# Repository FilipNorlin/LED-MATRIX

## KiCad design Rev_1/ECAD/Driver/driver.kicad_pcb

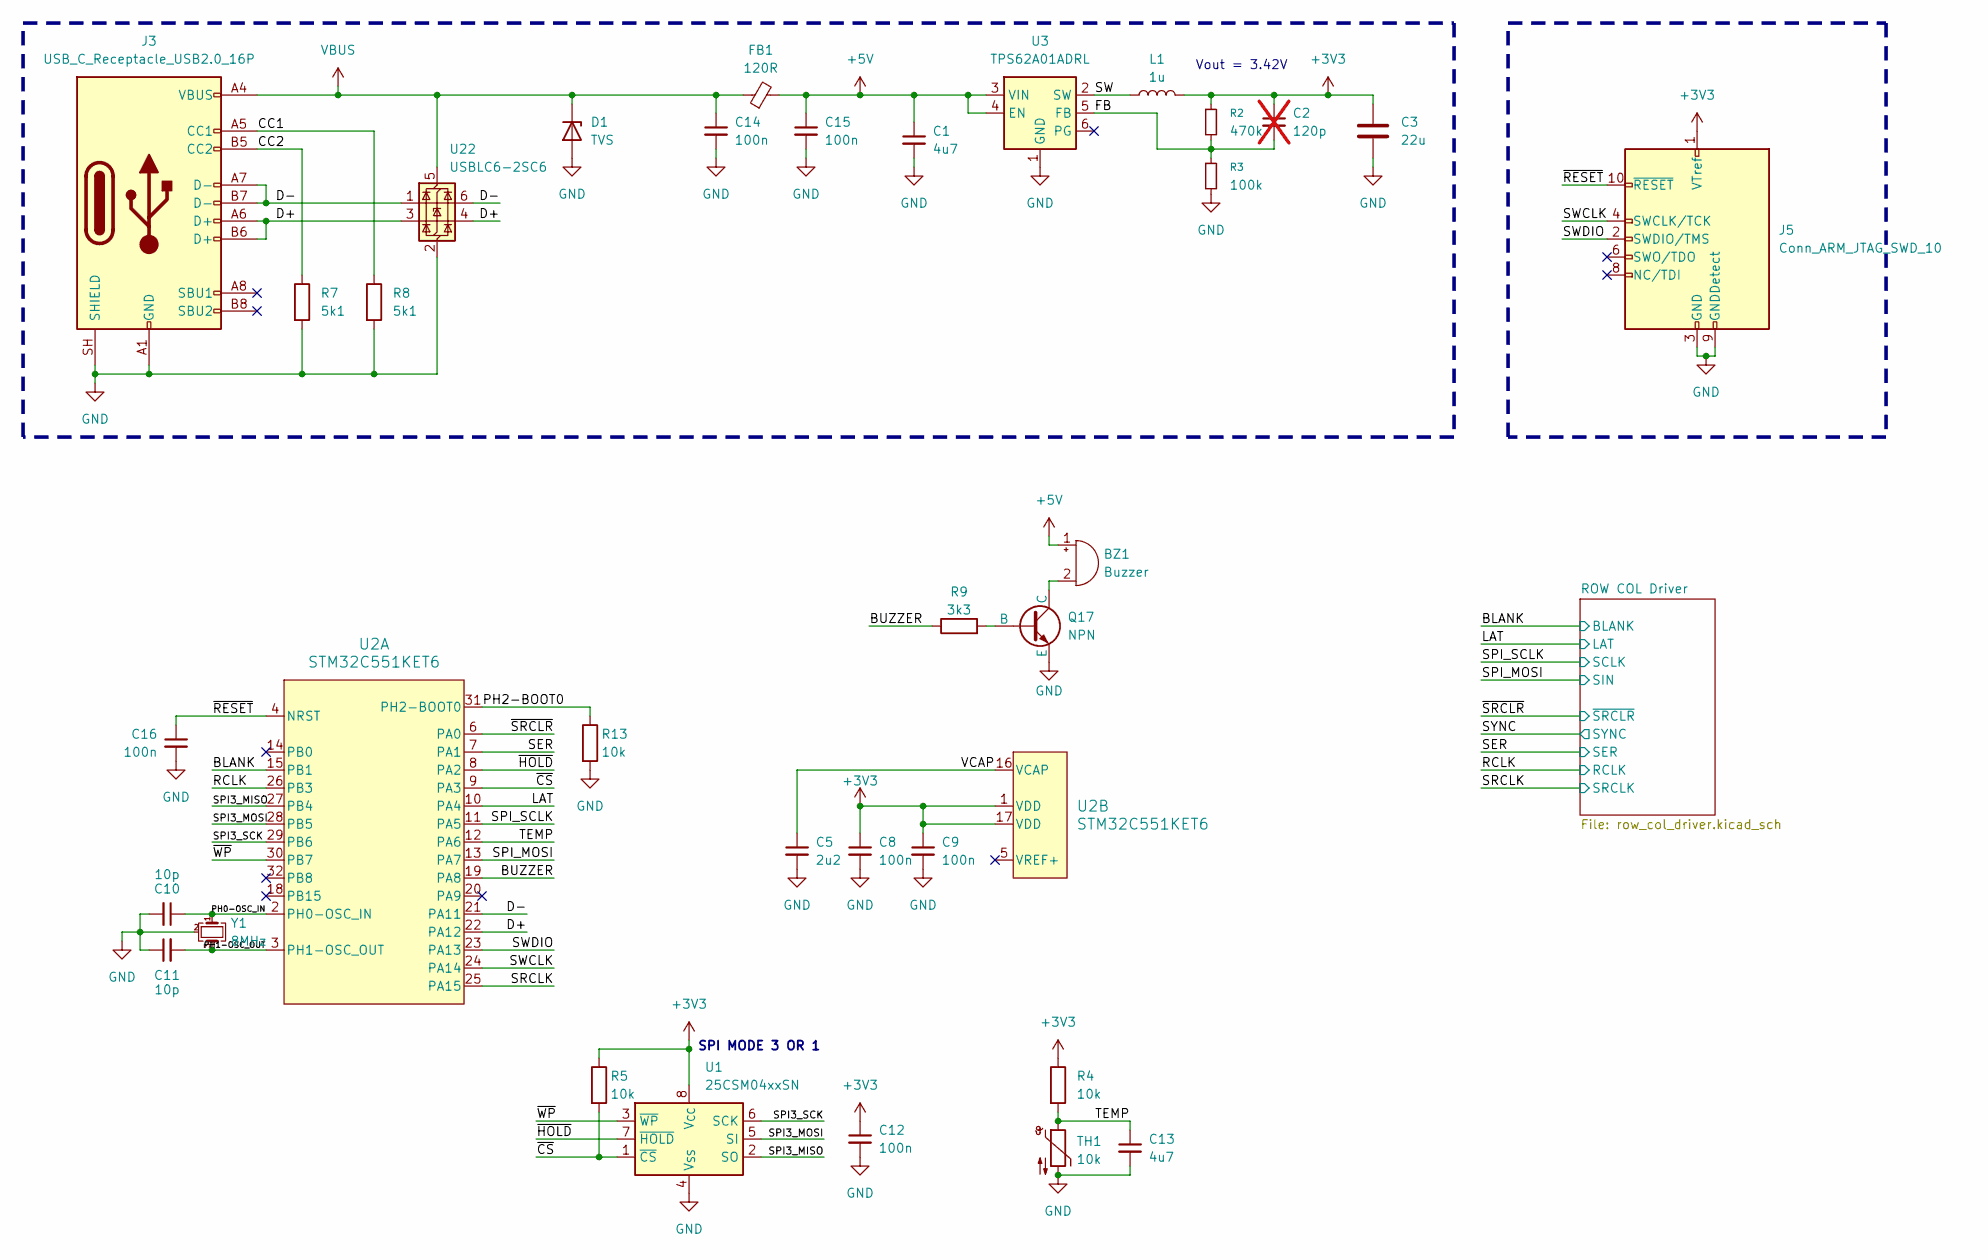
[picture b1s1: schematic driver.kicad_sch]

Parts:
BZ1: Buzzer; CPT120378SMTTR
C1, C13: 4u7; C_0805_2012Metric
C2: 120p; C_0603_1608Metric; not fitted
C3: 22u; C_0805_2012Metric
C5: 2u2; C_0603_1608Metric
C8, C9, C12, C14, C15: 100n; C_0805_2012Metric
C10, C11: 10p; C_0603_1608Metric
C16: 100n; C_0603_1608Metric
D1: TVS; D_SOD-123F
FB1: 120R; L_0805_2012Metric
J3: USB_C_Receptacle_USB2.0_16P; USB_C_Receptacle_GCT_USB4105-xx-A_16P_TopMnt_Horizontal
J5: Conn_ARM_JTAG_SWD_10; PinHeader_2x05_P1.27mm_Vertical_SMD
L1: 1u; L_0805_2012Metric; Mouser No: 187-CB201210AG1R0MPE
Q17: NPN; SOT-23
R2: 470k; R_0603_1608Metric_Pad0.98x0.95mm_HandSolder
R3: 100k; R_0805_2012Metric
R4, R5, R13: 10k; R_0805_2012Metric
R7, R8: 5k1; R_0805_2012Metric
R9: 3k3; R_0603_1608Metric
TH1: 10k; R_0603_1608Metric
U1: 25CSM04xxSN; SOIC-8_3.9x4.9mm_P1.27mm
U2: STM32C551KET6; LQFP-32_7x7mm_P0.8mm
U3: TPS62A01ADRL; SOT-563
U22: USBLC6-2SC6; SOT-23-6
Y1: 8MHz; Crystal_SMD_3225-4Pin_3.2x2.5mm

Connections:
+3V3: C2.1, C3.1, C8.1, C9.1, C12.1, J5.1 (VTref), L1.2, R2.1, R4.1, R5.1, U1.8 (V_{CC}), U2.1 (VDD), U2.17 (VDD); also elsewhere on the board
+5V: BZ1.1 (+), C1.1, C15.1, FB1.2, U3.3 (VIN), U3.4 (EN)
/BLANK: U2.15 (PB1); also elsewhere on the board
/BUZZER: R9.1, U2.19 (PA8)
/CC1: J3.A5 (CC1), R8.1
/CC2: J3.B5 (CC2), R7.1
/D+: J3.A6 (D+), J3.B6 (D+), U2.22 (PA12), U22.3 (I/O2), U22.4 (I/O2)
/D-: J3.A7 (D-), J3.B7 (D-), U2.21 (PA11), U22.1 (I/O1), U22.6 (I/O1)
/FB: C2.2, R2.2, R3.1, U3.5 (FB)
/LAT: U2.10 (PA4); also elsewhere on the board
/PH0-OSC_IN: C10.1, U2.2 (PH0-OSC_IN), Y1.1
/PH1-OSC_OUT: C11.2, U2.3 (PH1-OSC_OUT), Y1.3
/PH2-BOOT0: R13.1, U2.31 (PH2-BOOT0)
/RCLK: U2.26 (PB3); also elsewhere on the board
/SER: U2.7 (PA1); also elsewhere on the board
/SPI3_MISO: U1.2 (SO), U2.27 (PB4)
/SPI3_MOSI: U1.5 (SI), U2.28 (PB5)
/SPI3_SCK: U1.6 (SCK), U2.29 (PB6)
/SPI_MOSI: U2.13 (PA7); also elsewhere on the board
/SPI_SCLK: U2.11 (PA5); also elsewhere on the board
/SRCLK: U2.25 (PA15); also elsewhere on the board
/SW: L1.1, U3.2 (SW)
/SWCLK: J5.4 (SWCLK/TCK), U2.24 (PA14)
/SWDIO: J5.2 (SWDIO/TMS), U2.23 (PA13)
/TEMP: C13.1, R4.2, TH1.1, U2.12 (PA6)
/VCAP: C5.1, U2.16 (VCAP)
/~CS: R5.2, U1.1 (~CS), U2.9 (PA3)
/~HOLD: U1.7 (~HOLD), U2.8 (PA2)
/~RESET: C16.1, J5.10 (~RESET), U2.4 (NRST)
/~SRCLR: U2.6 (PA0); also elsewhere on the board
/~WP: U1.3 (~WP), U2.30 (PB7)
GND: C1.2, C3.2, C5.2, C8.2, C9.2, C10.2, C11.1, C12.2, C13.2, C14.2, C15.2, C16.2, D1.2 (A), J3.A1 (GND), J3.A12 (GND), J3.B1 (GND), J3.B12 (GND), J3.SH (SHIELD), J5.3 (GND), J5.5 (GND), J5.9 (GNDDetect), Q17.3 (E), R3.2, R7.2, R8.2, R13.2, TH1.2, U1.4 (V_{SS}), U3.1 (GND), U22.2 (GND), Y1.2 (G), Y1.4 (G); also elsewhere on the board
unnamed: BZ1.2 (-), Q17.1 (C)
unnamed: Q17.2 (B), R9.2
VBUS: C14.1, D1.1 (K), FB1.1, J3.A4 (VBUS), J3.A9 (VBUS), J3.B4 (VBUS), J3.B9 (VBUS), U22.5 (VBUS)

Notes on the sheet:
Vout = 3.42V
SPI MODE 3 OR 1

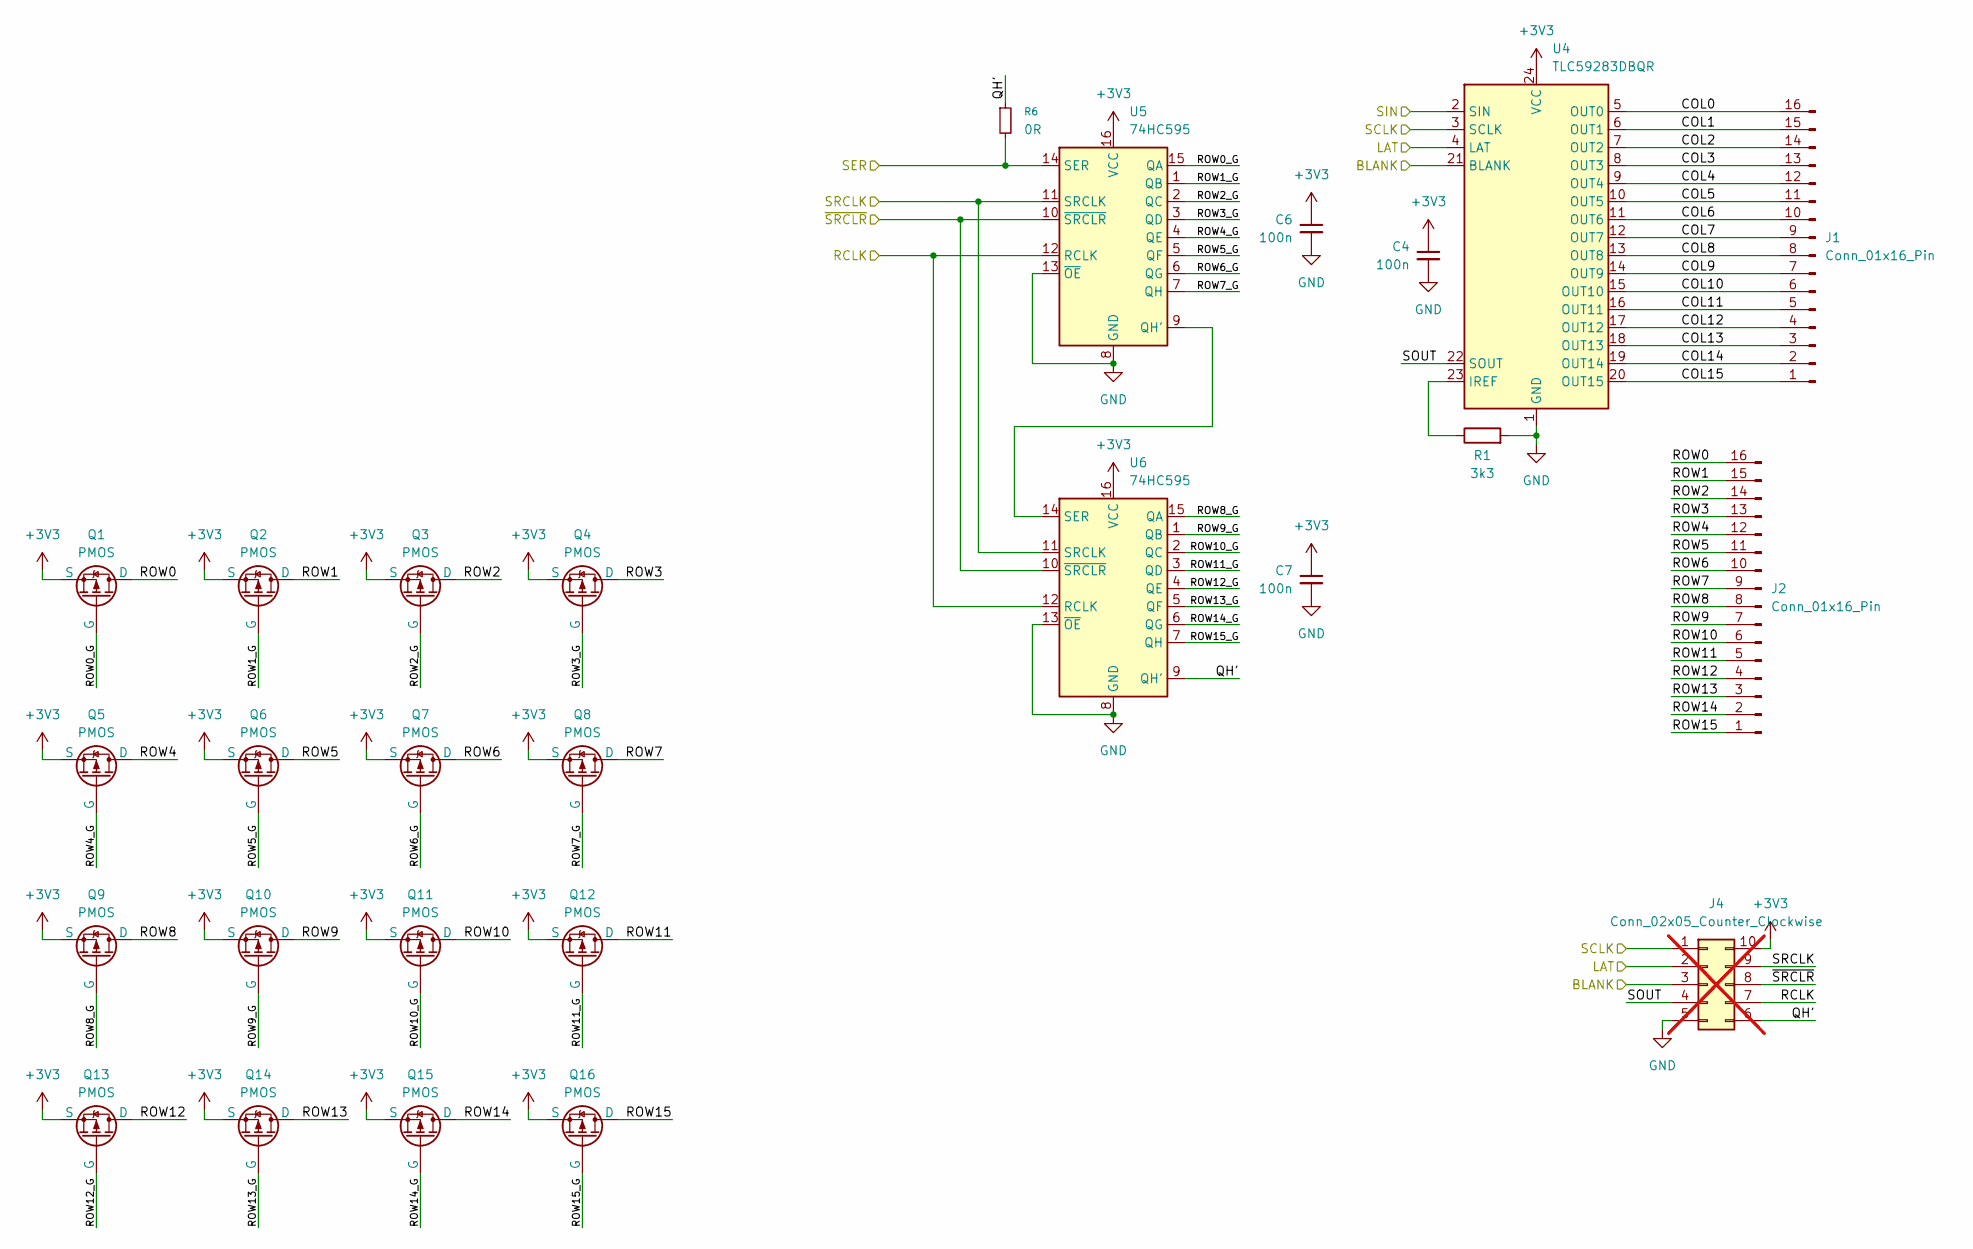
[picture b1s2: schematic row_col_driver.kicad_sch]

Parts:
C4, C6, C7: 100n; C_0805_2012Metric
J1, J2: Conn_01x16_Pin; PinSocket_1x16_P2.54mm_Vertical
J4: Conn_02x05_Counter_Clockwise; not fitted
Q1, Q2, Q3, Q4, Q5, Q6, Q7, Q8, Q9, Q10, Q11, Q12, Q13, Q14, Q15, Q16: PMOS; SOT-23
R1: 3k3; R_0603_1608Metric
R6: 0R; R_0603_1608Metric
U4: TLC59283DBQR; QSOP-24_3.9x8.7mm_P0.635mm; Mouser Part Number 595-TLC59283DBQR
U5, U6: 74HC595; SOIC-16_3.9x9.9mm_P1.27mm

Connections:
+3V3: C4.1, C6.1, C7.1, J4.10, Q1.3 (S), Q2.3 (S), Q3.3 (S), Q4.3 (S), Q5.3 (S), Q6.3 (S), Q7.3 (S), Q8.3 (S), Q9.3 (S), Q10.3 (S), Q11.3 (S), Q12.3 (S), Q13.3 (S), Q14.3 (S), Q15.3 (S), Q16.3 (S), U4.24 (VCC), U5.16 (VCC), U6.16 (VCC); also elsewhere on the board
/BLANK: J4.3, U4.21 (BLANK); also elsewhere on the board
/LAT: J4.2, U4.4 (LAT); also elsewhere on the board
/RCLK: U5.12 (RCLK), U6.12 (RCLK); also elsewhere on the board
/ROW COL Driver/COL0: J1.16, U4.5 (OUT0)
/ROW COL Driver/COL1: J1.15, U4.6 (OUT1)
/ROW COL Driver/COL2: J1.14, U4.7 (OUT2)
/ROW COL Driver/COL3: J1.13, U4.8 (OUT3)
/ROW COL Driver/COL4: J1.12, U4.9 (OUT4)
/ROW COL Driver/COL5: J1.11, U4.10 (OUT5)
/ROW COL Driver/COL6: J1.10, U4.11 (OUT6)
/ROW COL Driver/COL7: J1.9, U4.12 (OUT7)
/ROW COL Driver/COL8: J1.8, U4.13 (OUT8)
/ROW COL Driver/COL9: J1.7, U4.14 (OUT9)
/ROW COL Driver/COL10: J1.6, U4.15 (OUT10)
/ROW COL Driver/COL11: J1.5, U4.16 (OUT11)
/ROW COL Driver/COL12: J1.4, U4.17 (OUT12)
/ROW COL Driver/COL13: J1.3, U4.18 (OUT13)
/ROW COL Driver/COL14: J1.2, U4.19 (OUT14)
/ROW COL Driver/COL15: J1.1, U4.20 (OUT15)
/ROW COL Driver/QH': J4.6, R6.1, U6.9 (QH')
/ROW COL Driver/ROW0: J2.16, Q1.1 (D)
/ROW COL Driver/ROW0_G: Q1.2 (G), U5.15 (QA)
/ROW COL Driver/ROW1: J2.15, Q2.1 (D)
/ROW COL Driver/ROW1_G: Q2.2 (G), U5.1 (QB)
/ROW COL Driver/ROW2: J2.14, Q3.1 (D)
/ROW COL Driver/ROW2_G: Q3.2 (G), U5.2 (QC)
/ROW COL Driver/ROW3: J2.13, Q4.1 (D)
/ROW COL Driver/ROW3_G: Q4.2 (G), U5.3 (QD)
/ROW COL Driver/ROW4: J2.12, Q5.1 (D)
/ROW COL Driver/ROW4_G: Q5.2 (G), U5.4 (QE)
/ROW COL Driver/ROW5: J2.11, Q6.1 (D)
/ROW COL Driver/ROW5_G: Q6.2 (G), U5.5 (QF)
/ROW COL Driver/ROW6: J2.10, Q7.1 (D)
/ROW COL Driver/ROW6_G: Q7.2 (G), U5.6 (QG)
/ROW COL Driver/ROW7: J2.9, Q8.1 (D)
/ROW COL Driver/ROW7_G: Q8.2 (G), U5.7 (QH)
/ROW COL Driver/ROW8: J2.8, Q9.1 (D)
/ROW COL Driver/ROW8_G: Q9.2 (G), U6.15 (QA)
/ROW COL Driver/ROW9: J2.7, Q10.1 (D)
/ROW COL Driver/ROW9_G: Q10.2 (G), U6.1 (QB)
/ROW COL Driver/ROW10: J2.6, Q11.1 (D)
/ROW COL Driver/ROW10_G: Q11.2 (G), U6.2 (QC)
/ROW COL Driver/ROW11: J2.5, Q12.1 (D)
/ROW COL Driver/ROW11_G: Q12.2 (G), U6.3 (QD)
/ROW COL Driver/ROW12: J2.4, Q13.1 (D)
/ROW COL Driver/ROW12_G: Q13.2 (G), U6.4 (QE)
/ROW COL Driver/ROW13: J2.3, Q14.1 (D)
/ROW COL Driver/ROW13_G: Q14.2 (G), U6.5 (QF)
/ROW COL Driver/ROW14: J2.2, Q15.1 (D)
/ROW COL Driver/ROW14_G: Q15.2 (G), U6.6 (QG)
/ROW COL Driver/ROW15: J2.1, Q16.1 (D)
/ROW COL Driver/ROW15_G: Q16.2 (G), U6.7 (QH)
/ROW COL Driver/SOUT: J4.4, U4.22 (SOUT)
/SER: R6.2, U5.14 (SER); also elsewhere on the board
/SPI_MOSI: U4.2 (SIN); also elsewhere on the board
/SPI_SCLK: J4.1, U4.3 (SCLK); also elsewhere on the board
/SRCLK: U5.11 (SRCLK), U6.11 (SRCLK); also elsewhere on the board
/~SRCLR: U5.10 (~SRCLR), U6.10 (~SRCLR); also elsewhere on the board
GND: C4.2, C6.2, C7.2, J4.5, R1.2, U4.1 (GND), U5.8 (GND), U5.13 (~OE), U6.8 (GND), U6.13 (~OE); also elsewhere on the board
unnamed: R1.1, U4.23 (IREF)
unnamed: U5.9 (QH'), U6.14 (SER)

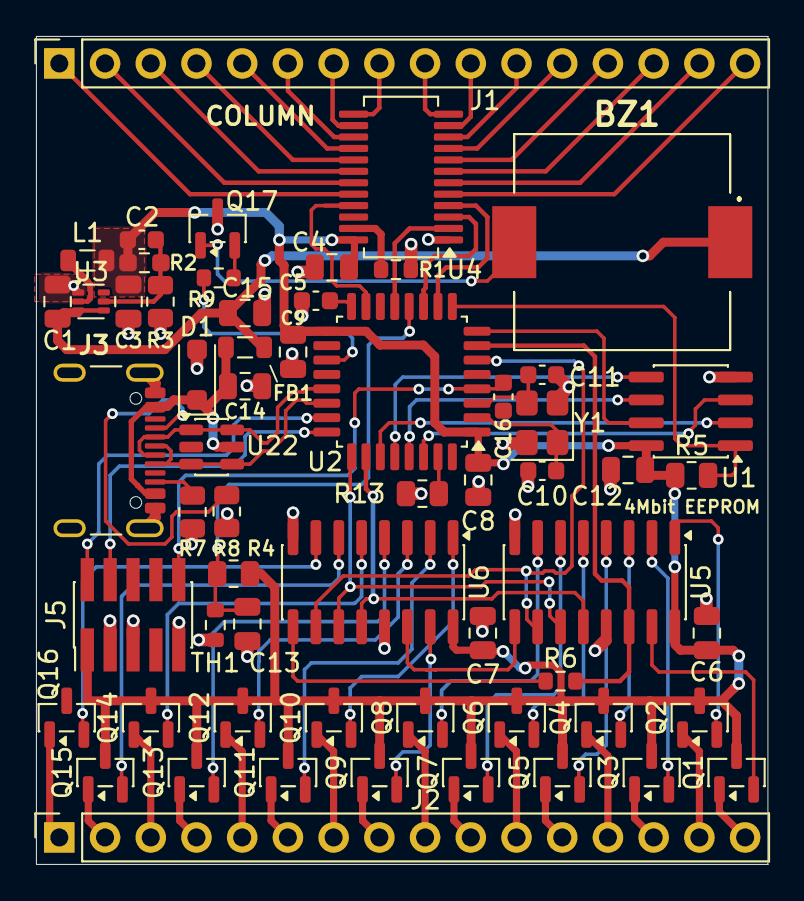
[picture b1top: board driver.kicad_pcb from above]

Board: 4 copper layers, 40.6 x 46.0 mm, 60 parts (0 on the bottom side), 86 nets.

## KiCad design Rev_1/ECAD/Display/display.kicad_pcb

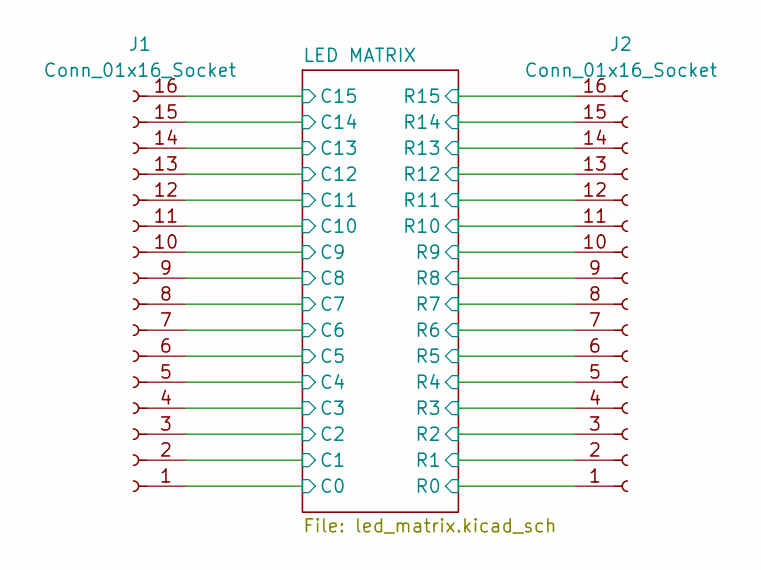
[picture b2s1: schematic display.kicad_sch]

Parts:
J1: Conn_01x16_Socket; PinHeader_1x16_P2.54mm_Vertical
J2: Conn_01x16_Socket; PinHeader_1x16_P2.54mm_Vertical_SMD_Pin1Left

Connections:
/LED MATRIX/C0: J1.1; also elsewhere on the board
/LED MATRIX/C1: J1.2; also elsewhere on the board
/LED MATRIX/C2: J1.3; also elsewhere on the board
/LED MATRIX/C3: J1.4; also elsewhere on the board
/LED MATRIX/C4: J1.5; also elsewhere on the board
/LED MATRIX/C5: J1.6; also elsewhere on the board
/LED MATRIX/C6: J1.7; also elsewhere on the board
/LED MATRIX/C7: J1.8; also elsewhere on the board
/LED MATRIX/C8: J1.9; also elsewhere on the board
/LED MATRIX/C9: J1.10; also elsewhere on the board
/LED MATRIX/C10: J1.11; also elsewhere on the board
/LED MATRIX/C11: J1.12; also elsewhere on the board
/LED MATRIX/C12: J1.13; also elsewhere on the board
/LED MATRIX/C13: J1.14; also elsewhere on the board
/LED MATRIX/C14: J1.15; also elsewhere on the board
/LED MATRIX/C15: J1.16; also elsewhere on the board
/LED MATRIX/R0: J2.1; also elsewhere on the board
/LED MATRIX/R1: J2.2; also elsewhere on the board
/LED MATRIX/R2: J2.3; also elsewhere on the board
/LED MATRIX/R3: J2.4; also elsewhere on the board
/LED MATRIX/R4: J2.5; also elsewhere on the board
/LED MATRIX/R5: J2.6; also elsewhere on the board
/LED MATRIX/R6: J2.7; also elsewhere on the board
/LED MATRIX/R7: J2.8; also elsewhere on the board
/LED MATRIX/R8: J2.9; also elsewhere on the board
/LED MATRIX/R9: J2.10; also elsewhere on the board
/LED MATRIX/R10: J2.11; also elsewhere on the board
/LED MATRIX/R11: J2.12; also elsewhere on the board
/LED MATRIX/R12: J2.13; also elsewhere on the board
/LED MATRIX/R13: J2.14; also elsewhere on the board
/LED MATRIX/R14: J2.15; also elsewhere on the board
/LED MATRIX/R15: J2.16; also elsewhere on the board

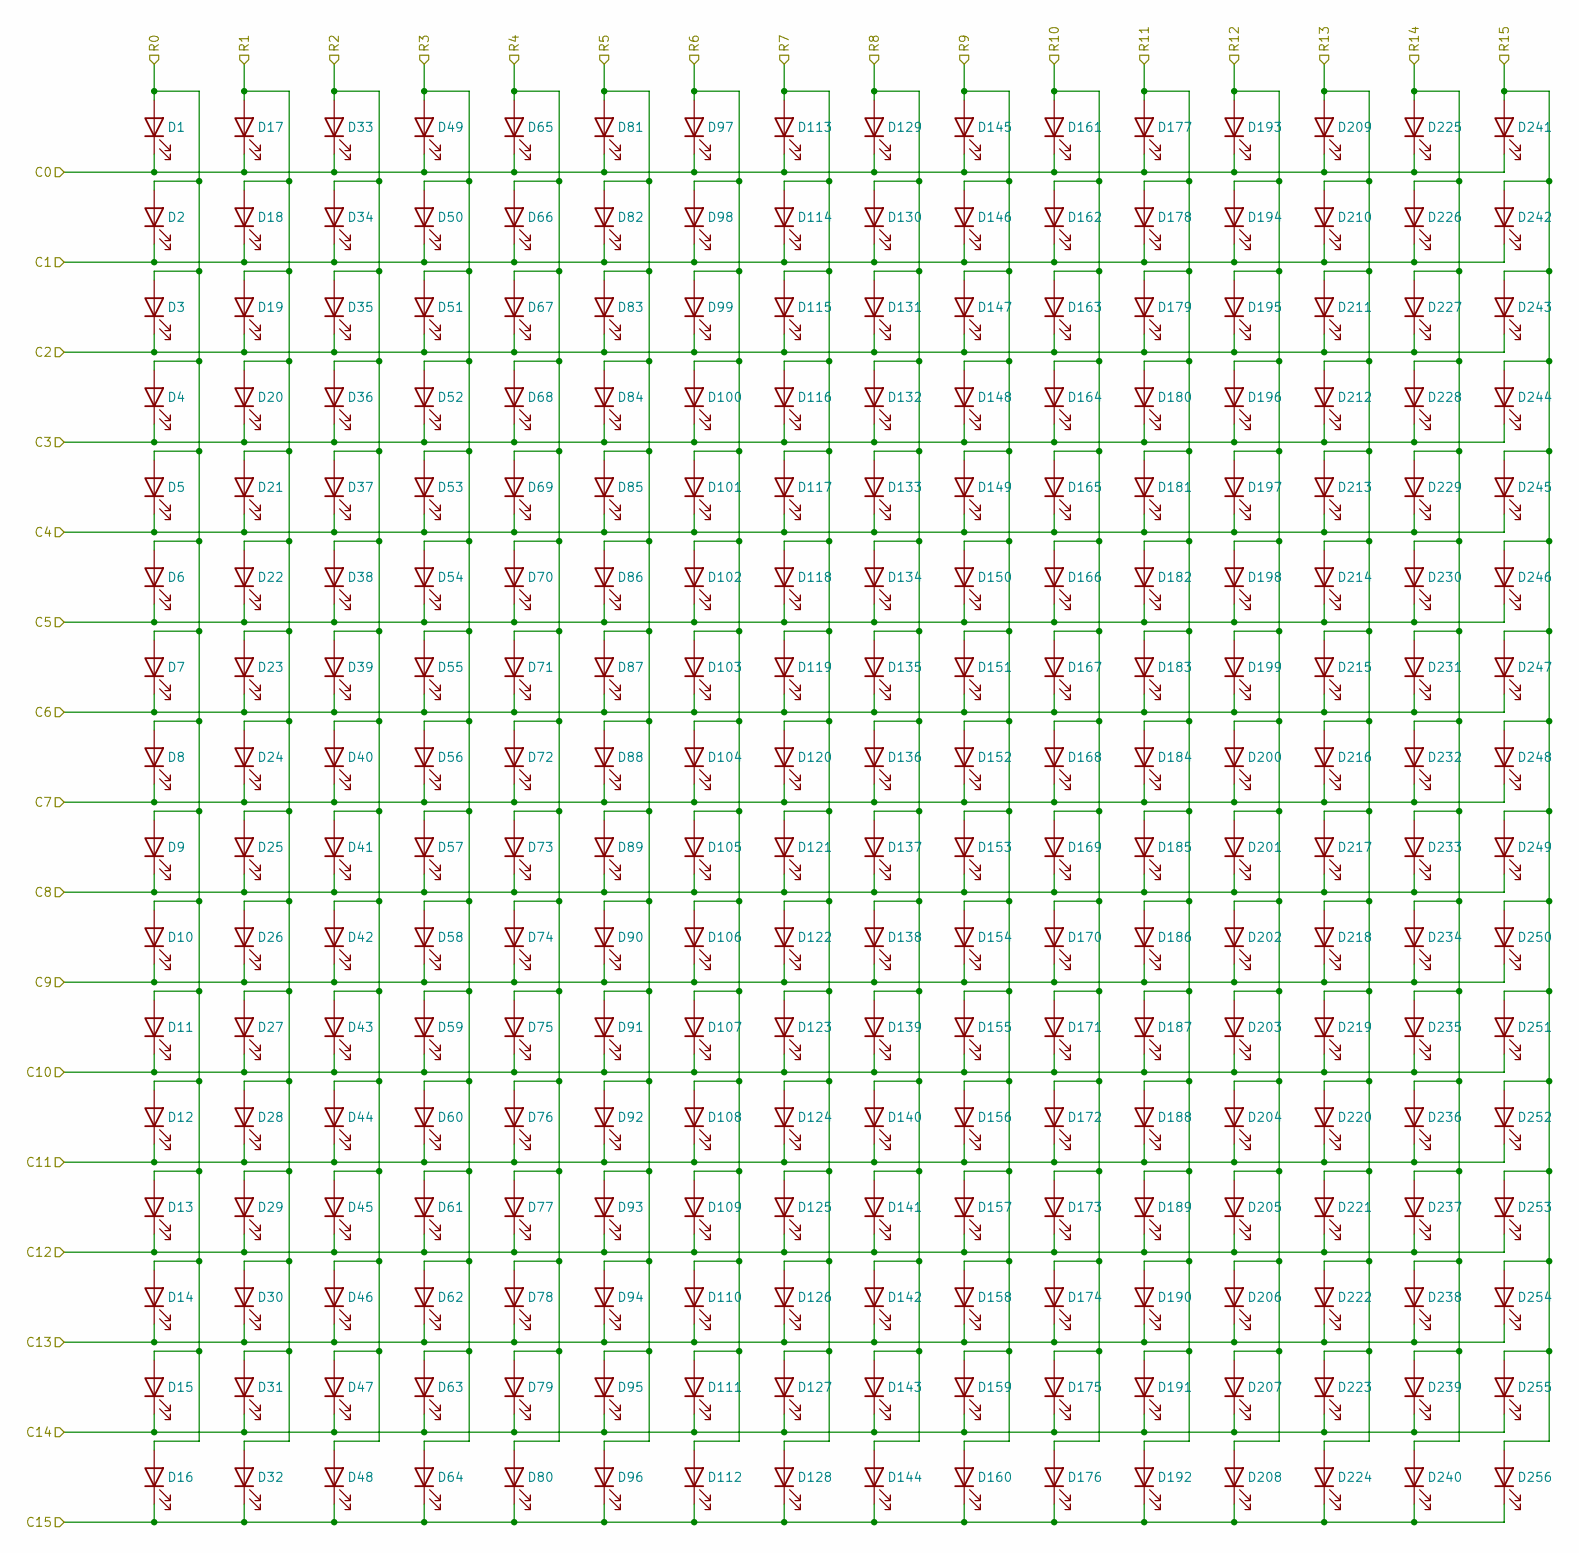
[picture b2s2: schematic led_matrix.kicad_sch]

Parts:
D1, D2, D3, D4, D5, D6, D7, D8, D9, D10, D11, D12, D13, D14, D15, D16, D17, D18, D19, D20, D21, D22, D23, D24, D25, D26, D27, D28, D29, D30, D31, D32, D33, D34, D35, D36, D37, D38, D39, D40, D41, D42, D43, D44, D45, D46, D47, D48, D49, D50, D51, D52, D53, D54, D55, D56, D57, D58, D59, D60, D61, D62, D63, D64, D65, D66, D67, D68, D69, D70, D71, D72, D73, D74, D75, D76, D77, D78, D79, D80, D81, D82, D83, D84, D85, D86, D87, D88, D89, D90, D91, D92, D93, D94, D95, D96, D97, D98, D99, D100, D101, D102, D103, D104, D105, D106, D107, D108, D109, D110, D111, D112, D113, D114, D115, D116, D117, D118, D119, D120, D121, D122, D123, D124, D125, D126, D127, D128, D129, D130, D131, D132, D133, D134, D135, D136, D137, D138, D139, D140, D141, D142, D143, D144, D145, D146, D147, D148, D149, D150, D151, D152, D153, D154, D155, D156, D157, D158, D159, D160, D161, D162, D163, D164, D165, D166, D167, D168, D169, D170, D171, D172, D173, D174, D175, D176, D177, D178, D179, D180, D181, D182, D183, D184, D185, D186, D187, D188, D189, D190, D191, D192, D193, D194, D195, D196, D197, D198, D199, D200, D201, D202, D203, D204, D205, D206, D207, D208, D209, D210, D211, D212, D213, D214, D215, D216, D217, D218, D219, D220, D221, D222, D223, D224, D225, D226, D227, D228, D229, D230, D231, D232, D233, D234, D235, D236, D237, D238, D239, D240, D241, D242, D243, D244, D245, D246, D247, D248, D249, D250, D251, D252, D253, D254, D255, D256: LED; LED_0603_1608Metric

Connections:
/LED MATRIX/C0: D1.1 (K), D17.1 (K), D33.1 (K), D49.1 (K), D65.1 (K), D81.1 (K), D97.1 (K), D113.1 (K), D129.1 (K), D145.1 (K), D161.1 (K), D177.1 (K), D193.1 (K), D209.1 (K), D225.1 (K), D241.1 (K); also elsewhere on the board
/LED MATRIX/C1: D2.1 (K), D18.1 (K), D34.1 (K), D50.1 (K), D66.1 (K), D82.1 (K), D98.1 (K), D114.1 (K), D130.1 (K), D146.1 (K), D162.1 (K), D178.1 (K), D194.1 (K), D210.1 (K), D226.1 (K), D242.1 (K); also elsewhere on the board
/LED MATRIX/C2: D3.1 (K), D19.1 (K), D35.1 (K), D51.1 (K), D67.1 (K), D83.1 (K), D99.1 (K), D115.1 (K), D131.1 (K), D147.1 (K), D163.1 (K), D179.1 (K), D195.1 (K), D211.1 (K), D227.1 (K), D243.1 (K); also elsewhere on the board
/LED MATRIX/C3: D4.1 (K), D20.1 (K), D36.1 (K), D52.1 (K), D68.1 (K), D84.1 (K), D100.1 (K), D116.1 (K), D132.1 (K), D148.1 (K), D164.1 (K), D180.1 (K), D196.1 (K), D212.1 (K), D228.1 (K), D244.1 (K); also elsewhere on the board
/LED MATRIX/C4: D5.1 (K), D21.1 (K), D37.1 (K), D53.1 (K), D69.1 (K), D85.1 (K), D101.1 (K), D117.1 (K), D133.1 (K), D149.1 (K), D165.1 (K), D181.1 (K), D197.1 (K), D213.1 (K), D229.1 (K), D245.1 (K); also elsewhere on the board
/LED MATRIX/C5: D6.1 (K), D22.1 (K), D38.1 (K), D54.1 (K), D70.1 (K), D86.1 (K), D102.1 (K), D118.1 (K), D134.1 (K), D150.1 (K), D166.1 (K), D182.1 (K), D198.1 (K), D214.1 (K), D230.1 (K), D246.1 (K); also elsewhere on the board
/LED MATRIX/C6: D7.1 (K), D23.1 (K), D39.1 (K), D55.1 (K), D71.1 (K), D87.1 (K), D103.1 (K), D119.1 (K), D135.1 (K), D151.1 (K), D167.1 (K), D183.1 (K), D199.1 (K), D215.1 (K), D231.1 (K), D247.1 (K); also elsewhere on the board
/LED MATRIX/C7: D8.1 (K), D24.1 (K), D40.1 (K), D56.1 (K), D72.1 (K), D88.1 (K), D104.1 (K), D120.1 (K), D136.1 (K), D152.1 (K), D168.1 (K), D184.1 (K), D200.1 (K), D216.1 (K), D232.1 (K), D248.1 (K); also elsewhere on the board
/LED MATRIX/C8: D9.1 (K), D25.1 (K), D41.1 (K), D57.1 (K), D73.1 (K), D89.1 (K), D105.1 (K), D121.1 (K), D137.1 (K), D153.1 (K), D169.1 (K), D185.1 (K), D201.1 (K), D217.1 (K), D233.1 (K), D249.1 (K); also elsewhere on the board
/LED MATRIX/C9: D10.1 (K), D26.1 (K), D42.1 (K), D58.1 (K), D74.1 (K), D90.1 (K), D106.1 (K), D122.1 (K), D138.1 (K), D154.1 (K), D170.1 (K), D186.1 (K), D202.1 (K), D218.1 (K), D234.1 (K), D250.1 (K); also elsewhere on the board
/LED MATRIX/C10: D11.1 (K), D27.1 (K), D43.1 (K), D59.1 (K), D75.1 (K), D91.1 (K), D107.1 (K), D123.1 (K), D139.1 (K), D155.1 (K), D171.1 (K), D187.1 (K), D203.1 (K), D219.1 (K), D235.1 (K), D251.1 (K); also elsewhere on the board
/LED MATRIX/C11: D12.1 (K), D28.1 (K), D44.1 (K), D60.1 (K), D76.1 (K), D92.1 (K), D108.1 (K), D124.1 (K), D140.1 (K), D156.1 (K), D172.1 (K), D188.1 (K), D204.1 (K), D220.1 (K), D236.1 (K), D252.1 (K); also elsewhere on the board
/LED MATRIX/C12: D13.1 (K), D29.1 (K), D45.1 (K), D61.1 (K), D77.1 (K), D93.1 (K), D109.1 (K), D125.1 (K), D141.1 (K), D157.1 (K), D173.1 (K), D189.1 (K), D205.1 (K), D221.1 (K), D237.1 (K), D253.1 (K); also elsewhere on the board
/LED MATRIX/C13: D14.1 (K), D30.1 (K), D46.1 (K), D62.1 (K), D78.1 (K), D94.1 (K), D110.1 (K), D126.1 (K), D142.1 (K), D158.1 (K), D174.1 (K), D190.1 (K), D206.1 (K), D222.1 (K), D238.1 (K), D254.1 (K); also elsewhere on the board
/LED MATRIX/C14: D15.1 (K), D31.1 (K), D47.1 (K), D63.1 (K), D79.1 (K), D95.1 (K), D111.1 (K), D127.1 (K), D143.1 (K), D159.1 (K), D175.1 (K), D191.1 (K), D207.1 (K), D223.1 (K), D239.1 (K), D255.1 (K); also elsewhere on the board
/LED MATRIX/C15: D16.1 (K), D32.1 (K), D48.1 (K), D64.1 (K), D80.1 (K), D96.1 (K), D112.1 (K), D128.1 (K), D144.1 (K), D160.1 (K), D176.1 (K), D192.1 (K), D208.1 (K), D224.1 (K), D240.1 (K), D256.1 (K); also elsewhere on the board
/LED MATRIX/R0: D1.2 (A), D2.2 (A), D3.2 (A), D4.2 (A), D5.2 (A), D6.2 (A), D7.2 (A), D8.2 (A), D9.2 (A), D10.2 (A), D11.2 (A), D12.2 (A), D13.2 (A), D14.2 (A), D15.2 (A), D16.2 (A); also elsewhere on the board
/LED MATRIX/R1: D17.2 (A), D18.2 (A), D19.2 (A), D20.2 (A), D21.2 (A), D22.2 (A), D23.2 (A), D24.2 (A), D25.2 (A), D26.2 (A), D27.2 (A), D28.2 (A), D29.2 (A), D30.2 (A), D31.2 (A), D32.2 (A); also elsewhere on the board
/LED MATRIX/R2: D33.2 (A), D34.2 (A), D35.2 (A), D36.2 (A), D37.2 (A), D38.2 (A), D39.2 (A), D40.2 (A), D41.2 (A), D42.2 (A), D43.2 (A), D44.2 (A), D45.2 (A), D46.2 (A), D47.2 (A), D48.2 (A); also elsewhere on the board
/LED MATRIX/R3: D49.2 (A), D50.2 (A), D51.2 (A), D52.2 (A), D53.2 (A), D54.2 (A), D55.2 (A), D56.2 (A), D57.2 (A), D58.2 (A), D59.2 (A), D60.2 (A), D61.2 (A), D62.2 (A), D63.2 (A), D64.2 (A); also elsewhere on the board
/LED MATRIX/R4: D65.2 (A), D66.2 (A), D67.2 (A), D68.2 (A), D69.2 (A), D70.2 (A), D71.2 (A), D72.2 (A), D73.2 (A), D74.2 (A), D75.2 (A), D76.2 (A), D77.2 (A), D78.2 (A), D79.2 (A), D80.2 (A); also elsewhere on the board
/LED MATRIX/R5: D81.2 (A), D82.2 (A), D83.2 (A), D84.2 (A), D85.2 (A), D86.2 (A), D87.2 (A), D88.2 (A), D89.2 (A), D90.2 (A), D91.2 (A), D92.2 (A), D93.2 (A), D94.2 (A), D95.2 (A), D96.2 (A); also elsewhere on the board
/LED MATRIX/R6: D97.2 (A), D98.2 (A), D99.2 (A), D100.2 (A), D101.2 (A), D102.2 (A), D103.2 (A), D104.2 (A), D105.2 (A), D106.2 (A), D107.2 (A), D108.2 (A), D109.2 (A), D110.2 (A), D111.2 (A), D112.2 (A); also elsewhere on the board
/LED MATRIX/R7: D113.2 (A), D114.2 (A), D115.2 (A), D116.2 (A), D117.2 (A), D118.2 (A), D119.2 (A), D120.2 (A), D121.2 (A), D122.2 (A), D123.2 (A), D124.2 (A), D125.2 (A), D126.2 (A), D127.2 (A), D128.2 (A); also elsewhere on the board
/LED MATRIX/R8: D129.2 (A), D130.2 (A), D131.2 (A), D132.2 (A), D133.2 (A), D134.2 (A), D135.2 (A), D136.2 (A), D137.2 (A), D138.2 (A), D139.2 (A), D140.2 (A), D141.2 (A), D142.2 (A), D143.2 (A), D144.2 (A); also elsewhere on the board
/LED MATRIX/R9: D145.2 (A), D146.2 (A), D147.2 (A), D148.2 (A), D149.2 (A), D150.2 (A), D151.2 (A), D152.2 (A), D153.2 (A), D154.2 (A), D155.2 (A), D156.2 (A), D157.2 (A), D158.2 (A), D159.2 (A), D160.2 (A); also elsewhere on the board
/LED MATRIX/R10: D161.2 (A), D162.2 (A), D163.2 (A), D164.2 (A), D165.2 (A), D166.2 (A), D167.2 (A), D168.2 (A), D169.2 (A), D170.2 (A), D171.2 (A), D172.2 (A), D173.2 (A), D174.2 (A), D175.2 (A), D176.2 (A); also elsewhere on the board
/LED MATRIX/R11: D177.2 (A), D178.2 (A), D179.2 (A), D180.2 (A), D181.2 (A), D182.2 (A), D183.2 (A), D184.2 (A), D185.2 (A), D186.2 (A), D187.2 (A), D188.2 (A), D189.2 (A), D190.2 (A), D191.2 (A), D192.2 (A); also elsewhere on the board
/LED MATRIX/R12: D193.2 (A), D194.2 (A), D195.2 (A), D196.2 (A), D197.2 (A), D198.2 (A), D199.2 (A), D200.2 (A), D201.2 (A), D202.2 (A), D203.2 (A), D204.2 (A), D205.2 (A), D206.2 (A), D207.2 (A), D208.2 (A); also elsewhere on the board
/LED MATRIX/R13: D209.2 (A), D210.2 (A), D211.2 (A), D212.2 (A), D213.2 (A), D214.2 (A), D215.2 (A), D216.2 (A), D217.2 (A), D218.2 (A), D219.2 (A), D220.2 (A), D221.2 (A), D222.2 (A), D223.2 (A), D224.2 (A); also elsewhere on the board
/LED MATRIX/R14: D225.2 (A), D226.2 (A), D227.2 (A), D228.2 (A), D229.2 (A), D230.2 (A), D231.2 (A), D232.2 (A), D233.2 (A), D234.2 (A), D235.2 (A), D236.2 (A), D237.2 (A), D238.2 (A), D239.2 (A), D240.2 (A); also elsewhere on the board
/LED MATRIX/R15: D241.2 (A), D242.2 (A), D243.2 (A), D244.2 (A), D245.2 (A), D246.2 (A), D247.2 (A), D248.2 (A), D249.2 (A), D250.2 (A), D251.2 (A), D252.2 (A), D253.2 (A), D254.2 (A), D255.2 (A), D256.2 (A); also elsewhere on the board

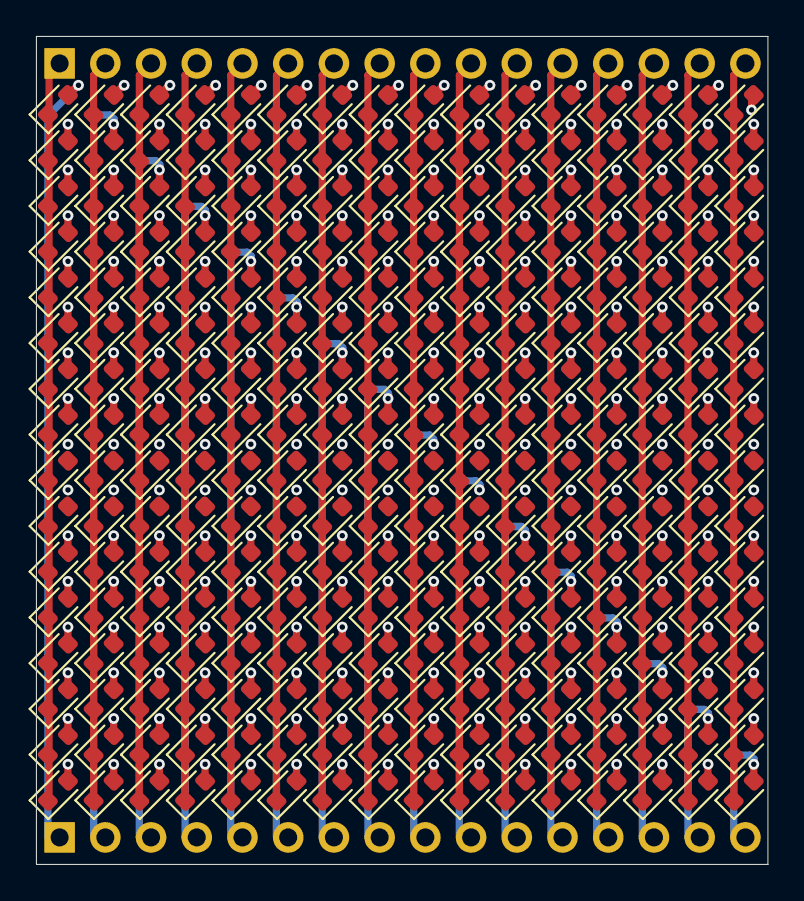
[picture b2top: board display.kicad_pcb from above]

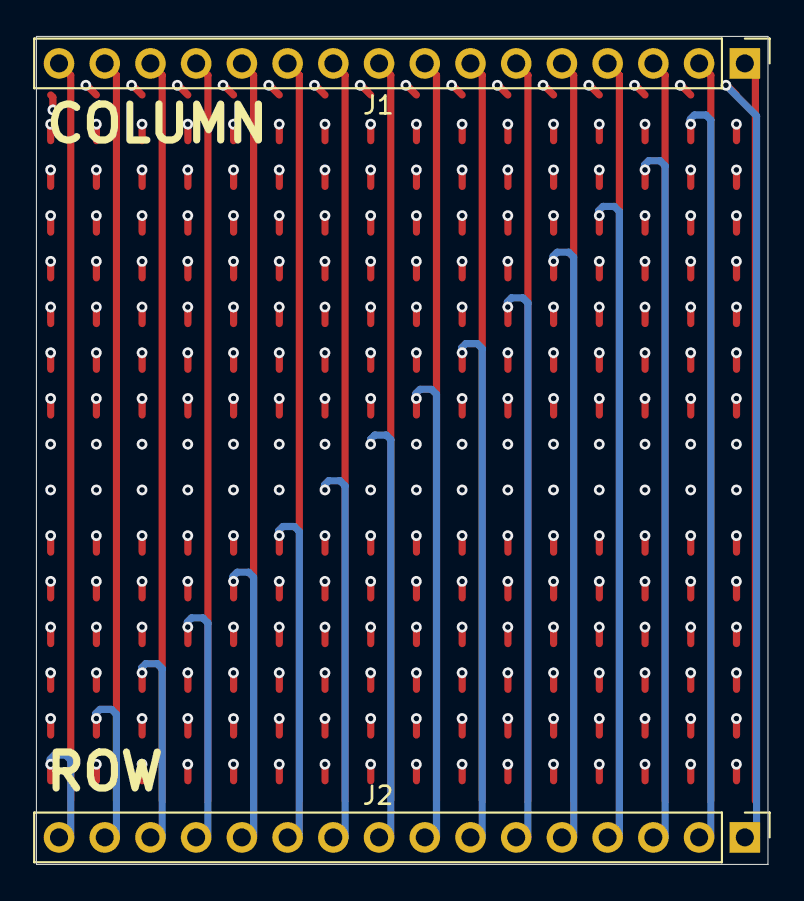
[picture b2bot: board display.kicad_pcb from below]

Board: 4 copper layers, 40.6 x 46.0 mm, 258 parts (2 on the bottom side), 32 nets.
